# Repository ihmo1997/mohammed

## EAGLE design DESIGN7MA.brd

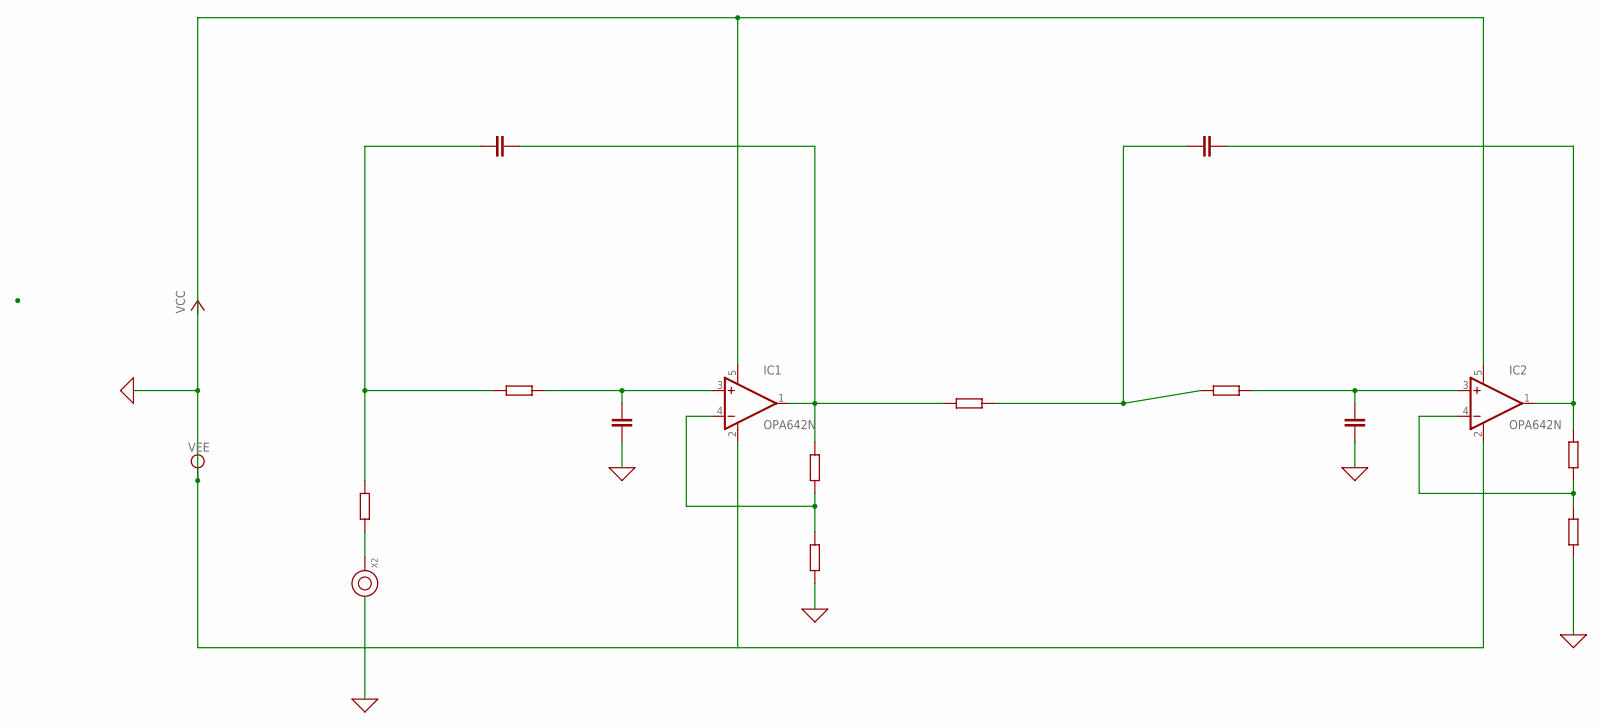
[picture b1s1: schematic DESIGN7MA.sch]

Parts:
IC1, IC2: OPA642N; SOT23-5
X2: BINDING-POST

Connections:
0: IC1.2 (V-), IC1.5 (V+), IC2.2 (V-), IC2.5 (V+)
unnamed: X2.1, X2.1_1, X2.1_2, X2.1_3, X2.1_4, X2.1_5, X2.1_6, X2.1_7, X2.1_8

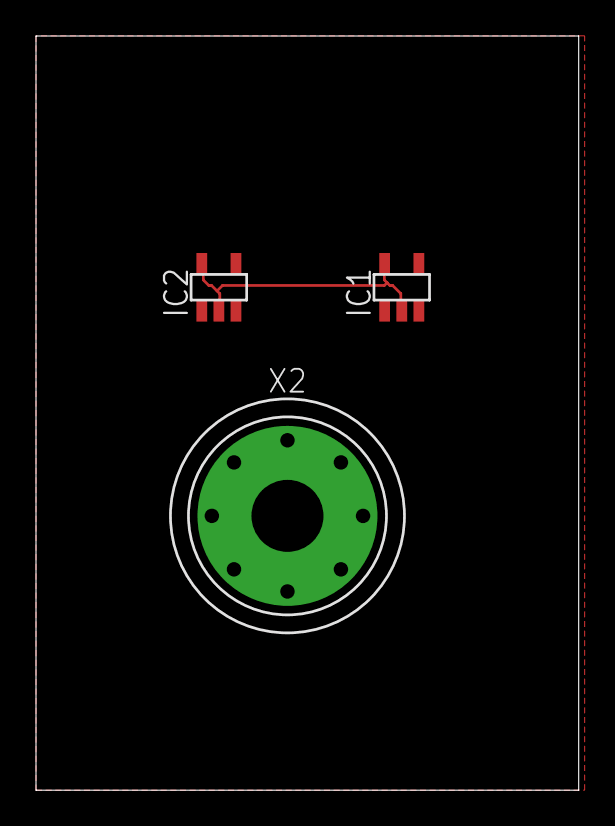
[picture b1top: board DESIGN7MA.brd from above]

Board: 2 copper layers, 30.2 x 41.9 mm, 3 parts (0 on the bottom side), 2 nets.
